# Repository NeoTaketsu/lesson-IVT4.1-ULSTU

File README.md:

# Список предметов и средств, по которым готовы лаб. работы

1. `{kicad-test}` Kicad - АКТП [Войт]
2. `{BD}` Erwin - ПИО [Токмаков]
3. `{igonin}` Proteus, MPLAB - АПМПС [Игонин]
4. `{network}` Cisco Packet Tracer - Сети и телекоммуникации [Мартынов]
5. `{security}` Python - Защита информации [Мартынов]
6. `{machine-learning}` Python - Интеллектуальный САПР [Святов]

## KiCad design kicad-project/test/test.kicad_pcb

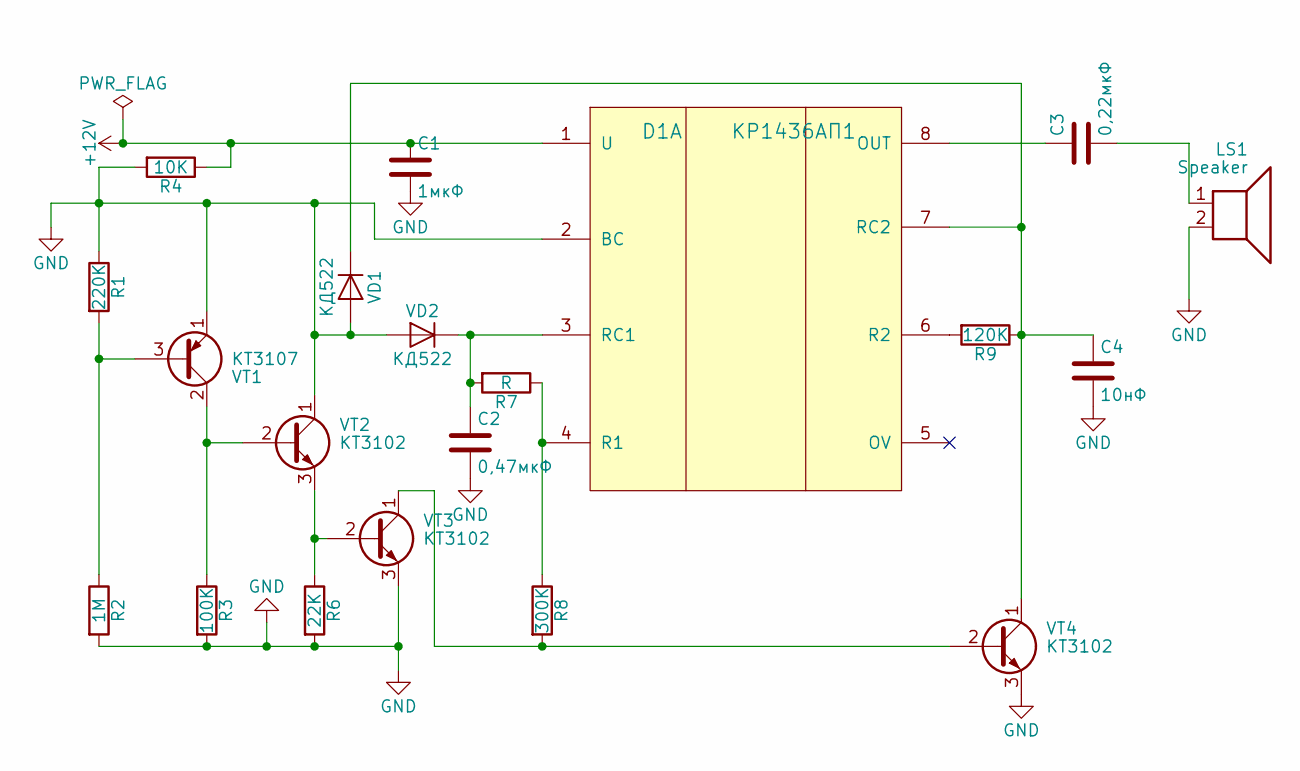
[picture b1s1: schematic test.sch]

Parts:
C1: 1мкФ; C_0805
C2: 0,47мкФ; C_0805
C3: 0,22мкФ; C_0805
C4: 10нФ; C_0805
D1: КР1436АП1; SOIC-8-N
LS1: Speaker; Seiko_MS621F
R1: 220K; R_0805
R2: 1M; R_0805
R3: 100K; R_0805
R4: 10K; R_0805
R6: 22K; R_0805
R7: R; R_0805
R8: 300K; R_0805
R9: 120K; R_0805
VD1, VD2: КД522; D_0805
VT1: KT3107; TO-92_Molded_Narrow
VT2, VT3, VT4: КТ3102; TO-92_Molded_Narrow

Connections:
+12V: C1.1, D1.1 (U), R4.1
GND: C1.2, C2.2, C4.2, D1.2 (BC), LS1.2, R1.1, R2.2, R3.2, R4.2, R6.2, VD1.2 (A), VD2.2 (A), VT1.1 (E), VT2.1 (C), VT3.3 (E), VT4.3 (E)
unnamed: C2.1, D1.3 (RC1), R7.2, VD2.1 (K)
unnamed: C3.1, D1.8 (OUT)
unnamed: C3.2, LS1.1
unnamed: C4.1, D1.7 (RC2), R9.1, VD1.1 (K), VT4.1 (C)
unnamed: D1.4 (R1), R7.1, R8.1
unnamed: D1.6 (R2), R9.2
unnamed: R1.2, R2.1, VT1.3 (B)
unnamed: R3.1, VT1.2 (C), VT2.2 (B)
unnamed: R6.1, VT2.3 (E), VT3.2 (B)
unnamed: R8.2, VT3.1 (C), VT4.2 (B)

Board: 2 copper layers, 20 parts (0 on the bottom side), 12 nets, no tracks yet.

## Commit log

2017-11-09 Kicad 1 лаба
2017-11-09 Readme update
2017-11-09 Базы данных
2017-11-09 Kicad начало 2 лабы
2017-11-10 Все лабы (1-3) Игонина
2017-11-10 Edit Readme
2017-11-13 Добавлены в индекс библиотеки kicad
2017-11-13 5 лаба БД ПИО
2017-11-15 1 Лаба по сетям
2017-11-15 Последняя 7 лаба
2017-11-17 1-3 лабы по Защите информации и Святову
2017-11-17 Лабы по защите информации 1 - 3
2017-11-17 Начало 4 лабы
2017-11-18 kicad 2 лаба
2017-11-20 4 Лаба (Кластеризация)
